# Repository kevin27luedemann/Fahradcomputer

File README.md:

# Fahradcomputer
Programm und andere Sachen fuer den Fahradcomputer

05.09.2015 Bibliotheken und Dataenblaetter hinzu

07.10.2015 MK2 begonnen und Programm portiert

13.12.2015 Softwareversion 3.0 begonnen: mit neuer Oberflächensteuerung

20.01.2016 GPS eingebunden und Aduino Library bereitgestellt

28.01.2016 cluster size von SD kann nicht so klein gewaehlt werden (512), wie muss, nachpruefen und SD gerecht einrichten

30.01.2016 SD Karte funktioniert seid 11:21 Uhr, noch nicht implementitert in FWCP

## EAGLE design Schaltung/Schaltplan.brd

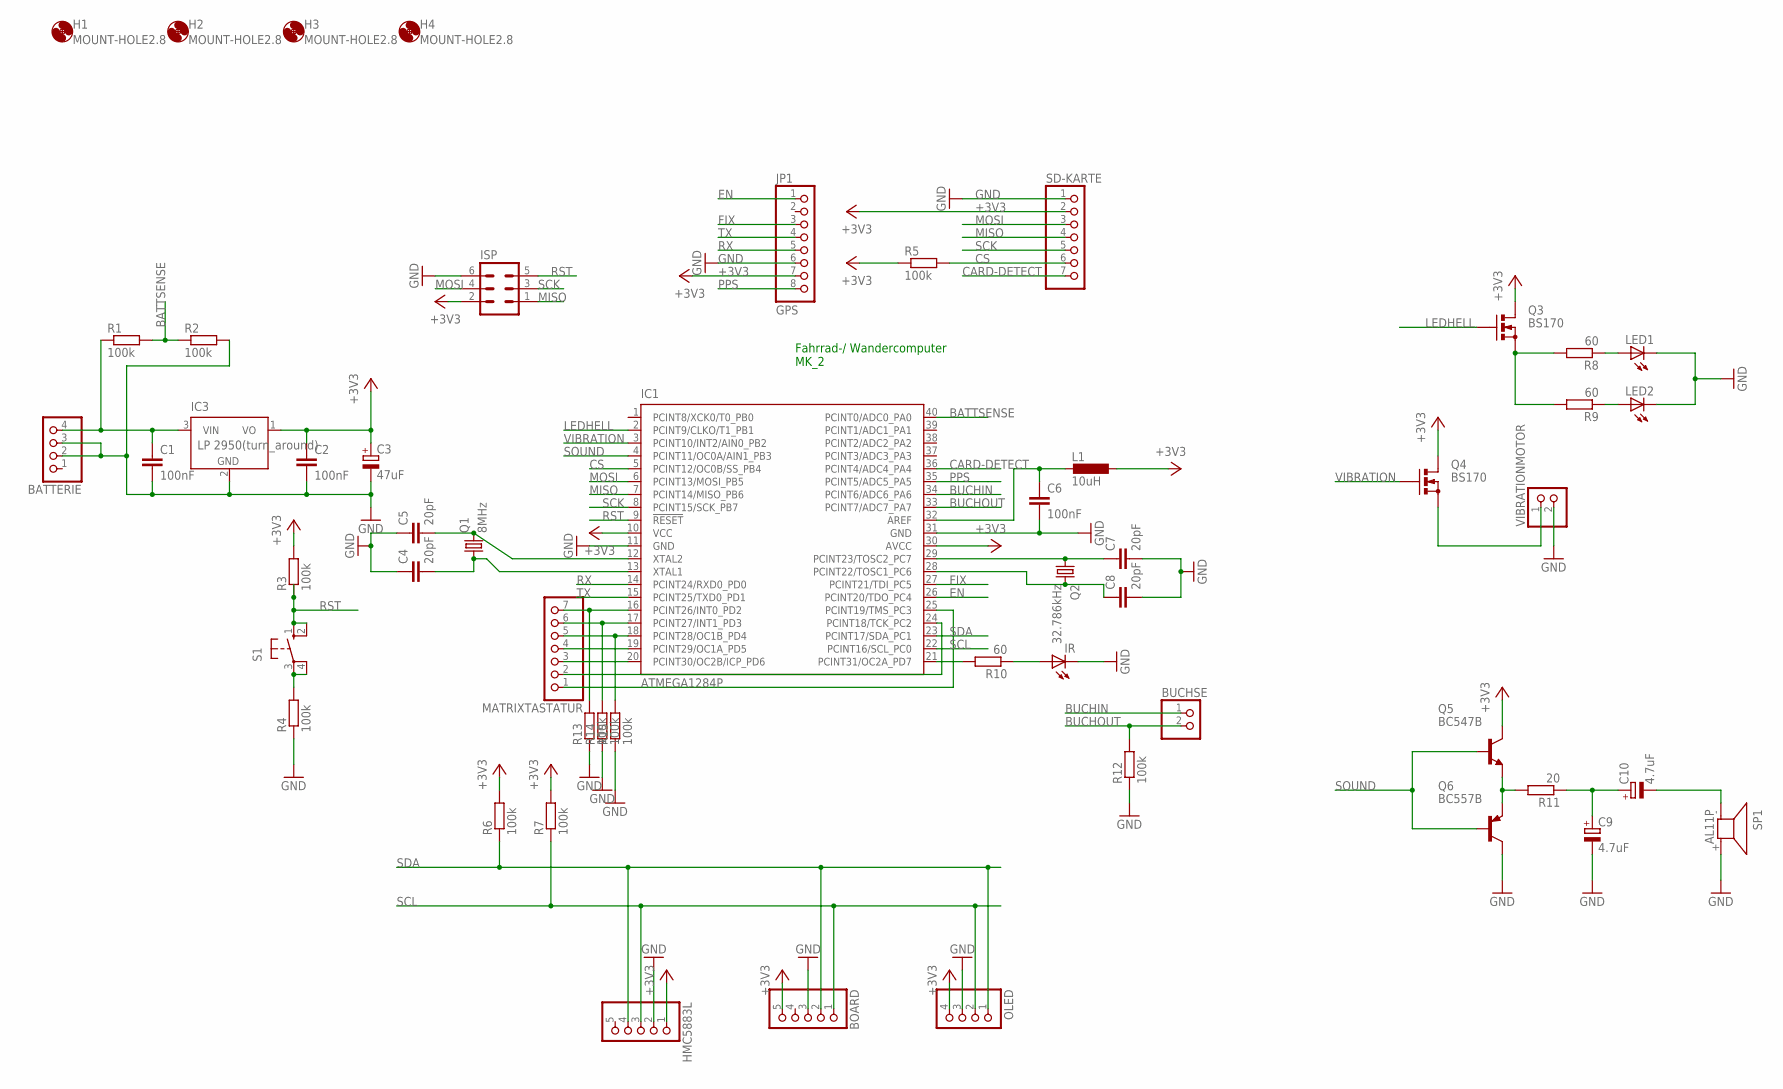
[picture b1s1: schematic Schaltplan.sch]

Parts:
BATTERIE: PINHD-1X4; 1X04
BOARD: PINHD-1X5; 1X05
BUCHSE: PINHD-1X2; 1X02
C1, C2, C6: 100nF; C025-024X044
C3: 47uF; E2,5-6
C4, C5, C7, C8: 20pF; C025-024X044
C9, C10: 4.7uF; E2,5-6
H1, H2, H3, H4: MOUNT-HOLE2.8; 2,8
HMC5883L: PINHD-1X5; 1X05
IC1: ATMEGA1284P; DIL40
IC3: LP 2950(turn_around); TO92
IR: LED3MM
ISP: ML6
JP1: GPS; 1X08
L1: 10uH; 0207/10
LED1, LED2: LED5MM
MATRIXTASTATUR: PINHD-1X7; 1X07
OLED: PINHD-1X4; 1X04
Q1: 8MHz; HC49/S
Q2: 32.786kHz; TC26V
Q3, Q4: BS170; SOT54E
Q5: BC547B; TO92
Q6: BC557B; TO92-EBC
R1, R2, R3, R4, R5, R6, R7, R12, R13, R14, R15: 100k; 0207/10
R8, R9, R10: 60; 0207/10
R11: 20; 0207/10
S1: 10-XX; B3F-10XX
SD-KARTE: PINHD-1X7; 1X07
SP1: AL11P
VIBRATIONMOTOR: PINHD-1X2; 1X02

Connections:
+3V3: BOARD.5, C2.1, C3.+, HMC5883L.1, IC1.10 (VCC), IC1.30 (AVCC), IC3.1 (VO), ISP.2, JP1.7, L1.1, OLED.4, Q3.D, Q4.D, Q5.3 (C), R3.2, R5.1, R6.2, R7.2, SD-KARTE.2
BATTSENSE: IC1.40 (PCINT0/ADC0_PA0), R1.2, R2.1
BUCHIN: BUCHSE.1, IC1.34 (PCINT6/ADC6_PA6)
BUCHOUT: BUCHSE.2, IC1.33 (PCINT7/ADC7_PA7), R12.2
CARD-DETECT: IC1.36 (PCINT4/ADC4_PA4), SD-KARTE.7
CS: IC1.5 (PCINT12/OC0B/SS_PB4), R5.2, SD-KARTE.6
EN: IC1.26 (PCINT20/TDO_PC4), JP1.1
FIX: IC1.27 (PCINT21/TDI_PC5), JP1.3
GND: BATTERIE.2, BATTERIE.3, BOARD.3, C1.2, C2.2, C3.-, C4.1, C5.1, C6.2, C7.2, C8.2, C9.-, HMC5883L.2, IC1.11 (GND), IC1.31 (GND), IC3.2 (GND), IR.K (C), ISP.6, JP1.6, LED1.K (C), LED2.K (C), OLED.3, Q6.C, R2.2, R4.1, R12.1, R13.1, R14.1, R15.1, SD-KARTE.1, SP1.+ (2), VIBRATIONMOTOR.2
LEDHELL: IC1.2 (PCINT9/CLKO/T1_PB1), Q3.G
MISO: IC1.7 (PCINT14/MISO_PB6), ISP.1, SD-KARTE.4
MOSI: IC1.6 (PCINT13/MOSI_PB5), ISP.4, SD-KARTE.3
unnamed: BATTERIE.4, C1.1, IC3.3 (VIN), R1.1
unnamed: C5.2, IC1.12 (XTAL2), Q1.2
unnamed: C7.1, IC1.29 (PCINT23/TOSC2_PC7), Q2.1
unnamed: C4.2, IC1.13 (XTAL1), Q1.1
unnamed: C8.1, IC1.28 (PCINT22/TOSC1_PC6), Q2.2
unnamed: R4.2, S1.3, S1.4 (P1)
unnamed: Q3.S, R8.2, R9.2
unnamed: C6.1, IC1.32 (AREF), L1.2
unnamed: LED1.A, R8.1
unnamed: LED2.A, R9.1
unnamed: IC1.16 (PCINT26/INT0_PD2), MATRIXTASTATUR.7, R13.2
unnamed: IC1.17 (PCINT27/INT1_PD3), MATRIXTASTATUR.6, R14.2
unnamed: IC1.18 (PCINT28/OC1B_PD4), MATRIXTASTATUR.5, R15.2
unnamed: Q4.S, VIBRATIONMOTOR.1
unnamed: IC1.19 (PCINT29/OC1A_PD5), MATRIXTASTATUR.4
unnamed: IC1.20 (PCINT30/OC2B/ICP_PD6), MATRIXTASTATUR.3
unnamed: IC1.24 (PCINT18/TCK_PC2), MATRIXTASTATUR.2
unnamed: IC1.25 (PCINT19/TMS_PC3), MATRIXTASTATUR.1
unnamed: IC1.21 (PCINT31/OC2A_PD7), R10.2
unnamed: IR.A, R10.1
unnamed: Q5.1 (E), Q6.E, R11.2
unnamed: C9.+, C10.+, R11.1
unnamed: C10.-, SP1.- (1)
PPS: IC1.35 (PCINT5/ADC5_PA5), JP1.8
RST: IC1.9 (!RESET), ISP.5, R3.1, S1.1 (S), S1.2 (S1)
RX: IC1.14 (PCINT24/RXD0_PD0), JP1.5
SCK: IC1.8 (PCINT15/SCK_PB7), ISP.3, SD-KARTE.5
SCL: BOARD.1, HMC5883L.3, IC1.22 (PCINT16/SCL_PC0), OLED.2, R7.1
SDA: BOARD.2, HMC5883L.4, IC1.23 (PCINT17/SDA_PC1), OLED.1, R6.1
SOUND: IC1.4 (PCINT11/OC0A/AIN1_PB3), Q5.2 (B), Q6.B
TX: IC1.15 (PCINT25/TXD0_PD1), JP1.4
VIBRATION: IC1.3 (PCINT10/INT2/AIN0_PB2), Q4.G

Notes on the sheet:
Fahrrad-/ Wandercomputer MK_2

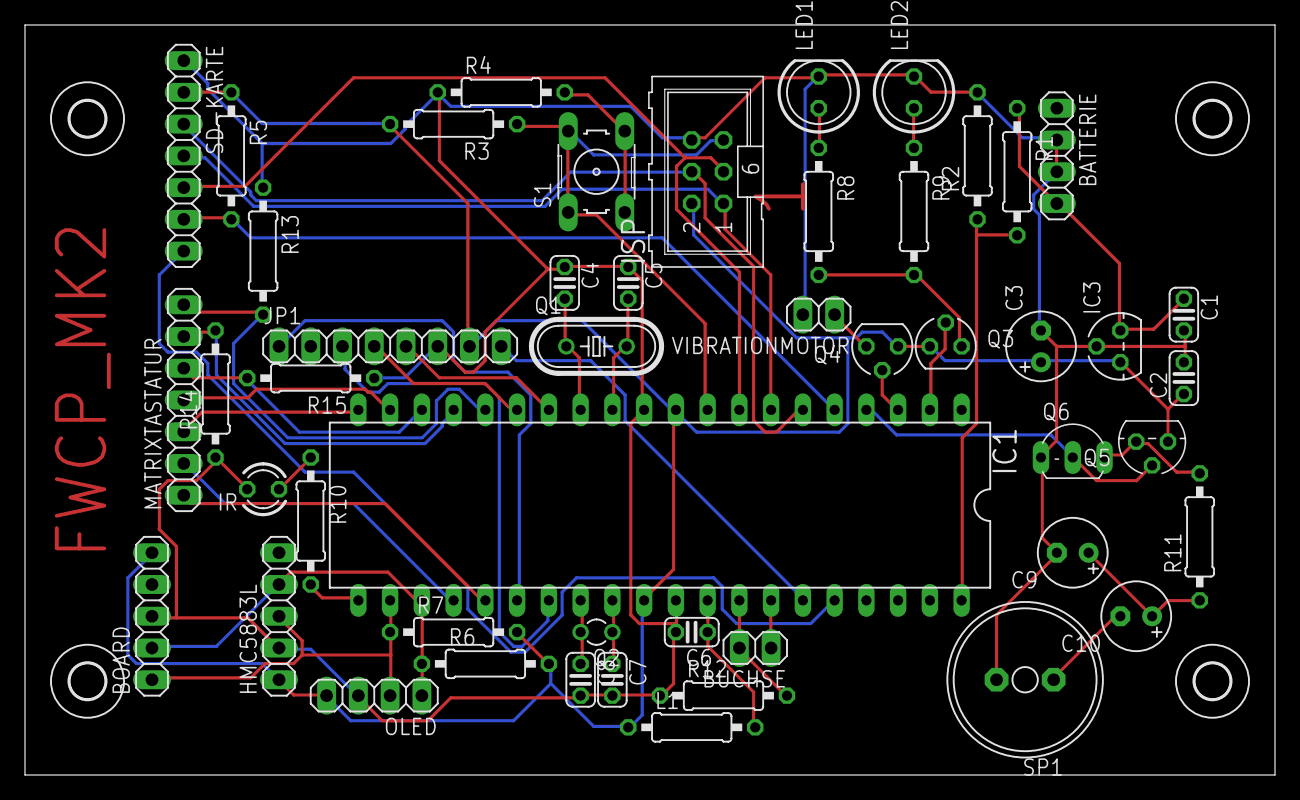
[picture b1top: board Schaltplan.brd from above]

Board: 2 copper layers, 100.0 x 60.0 mm, 53 parts (0 on the bottom side), 44 nets.

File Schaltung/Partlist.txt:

Partlist

Exported from Schaltplan.sch at 18.09.2015 10:32

EAGLE Version 7.3.0 Copyright (c) 1988-2015 CadSoft

Assembly variant: 

Part           Value                Device          Package      Library                 Sheet

BATTERIE                            PINHD-1X4       1X04         pinhead                 1
BOARD                               PINHD-1X5       1X05         pinhead                 1
BUCHSE                              PINHD-1X2       1X02         pinhead                 1
C1             100nF                C-EU025-024X044 C025-024X044 rcl                     1
C2             100nF                C-EU025-024X044 C025-024X044 rcl                     1
C3             47uF                 CPOL-EUE2.5-6   E2,5-6       rcl                     1
C4             20pF                 C-EU025-024X044 C025-024X044 rcl                     1
C5             20pF                 C-EU025-024X044 C025-024X044 rcl                     1
C6             100nF                C-EU025-024X044 C025-024X044 rcl                     1
C7             20pF                 C-EU025-024X044 C025-024X044 rcl                     1
C8             20pF                 C-EU025-024X044 C025-024X044 rcl                     1
C9             4.7uF                CPOL-EUE2.5-6   E2,5-6       rcl                     1
C10            4.7uF                CPOL-EUE2.5-6   E2,5-6       rcl                     1
HMC5883L                            PINHD-1X5       1X05         pinhead                 1
IC1            ATMEGA1284P          ATMEGA644-20PU  DIL40        atmel                   1
IC3            LP 2950(turn_around) LM2936Z-3.0     TO92         national-semiconductor  1
IR                                  LED3MM          LED3MM       led                     1
ISP                                 ML6             ML6          con-ml                  1
JP1            GPS                  PINHD-1X8       1X08         pinhead                 1
L1             10uH                 L-EU0207/10     0207/10      rcl                     1
LED1                                LED5MM          LED5MM       led                     1
LED2                                LED5MM          LED5MM       led                     1
MATRIXTASTATUR                      PINHD-1X7       1X07         pinhead                 1
OLED                                PINHD-1X4       1X04         pinhead                 1
Q1             8MHz                 CRYSTALHC49S    HC49/S       crystal                 1
Q2             32.786kHz            CRYSTALTC26V    TC26V        crystal                 1
Q3             BS170                BS170           SOT54E       transistor-small-signal 1
Q4             BS170                BS170           SOT54E       transistor-small-signal 1
Q5             BC547B               BC547B          TO92         transistor-npn          1
Q6             BC557B               BC557B          TO92-EBC     transistor-pnp          1
R1             100k                 R-EU_0207/10    0207/10      rcl                     1
R2             100k                 R-EU_0207/10    0207/10      rcl                     1
R3             100k                 R-EU_0207/10    0207/10      rcl                     1
R4             100k                 R-EU_0207/10    0207/10      rcl                     1
R5             100k                 R-EU_0207/10    0207/10      rcl                     1
R6             100k                 R-EU_0207/10    0207/10      rcl                     1
R7             100k                 R-EU_0207/10    0207/10      rcl                     1
R8             60                   R-EU_0207/10    0207/10      rcl                     1
R9             60                   R-EU_0207/10    0207/10      rcl                     1
R10            60                   R-EU_0207/10    0207/10      rcl                     1
R11            20                   R-EU_0207/10    0207/10      rcl                     1
R12            100k                 R-EU_0207/10    0207/10      rcl                     1
R13            100k                 R-EU_0207/10    0207/10      rcl                     1
R14            100k                 R-EU_0207/10    0207/10      rcl                     1
R15            100k                 R-EU_0207/10    0207/10      rcl                     1
S1                                  10-XX           B3F-10XX     switch-omron            1
SD-KARTE                            PINHD-1X7       1X07         pinhead                 1
SP1            AL11P                AL11P           AL11P        buzzer                  1
VIBRATIONMOTOR                      PINHD-1X2       1X02         pinhead                 1

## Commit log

2015-09-02 Programmhinzugefuegt
2015-09-05 Programm effizienter
2015-09-05 Fehler behoben
2015-09-06 Programm erweitert
2015-09-06 Datasheet hinzu
2015-09-07 RTC um Kalendermode erweitert und Fehler behoben
2015-09-07 Test
2015-09-07 README erweitert
2015-09-07 Datenblaetter fuer die neuen Sensoren hinzu
2015-09-07 Informationen fuer pedometer hinzugefuegt
2015-09-07 SCL Rate auf 400 kHz
2015-09-08 Class fuer den Drucksensor geschrieben, ohne Mode einstellungen bis jetzt einfuegen, wenn vorhanden und ausprobiert
2015-09-08 Stundenzeiger feinstrucktur ueber Minuten implementiert, zu dem Fehler in Druck behoben
2015-09-09 Fehler in Pressure.h behoben und Class fuer LSM303D angefangen
2015-09-09 datein hinzugefuegt
2015-09-09 Output class erstellt und angewendet auf LED und Vibrationsmotor. Beide in Hardware vorhanden.
2015-09-09 Fehler in Druckberechung nicht behoben
2015-09-10 Druckausganbe funktioniert und Oberflaeche geschrieben
2015-09-17 Altimeter impleentiert
2015-09-17 Materialliste hinzu
2015-09-17 Schaltung hinzugefuegt
2015-09-17 grosse Uhr hinzu
2015-09-17 reichelt Warenkorb hinzu
2015-09-18 Schaltung un d Board verandert
2015-09-18 Schaltplan/Board beim Hersteller hochgeladen
2015-09-18 Schaltplan und Board als PDF
2015-09-22 Licht an/aus eingebaut, strecke und maxgeschw ebenfalls
2015-09-23 neues update und zusaetzliche Fahrtzeit und loeschfunktion fuer die Werte im Speicher
2015-09-27 Oberflaechenverbesserung und Modus erweiterung. Bildsschirm aktualisiert nun so schnell wie moeglich
2015-09-28 Fahrad besser und Funktionsfaehig, noch kein live Test
2015-09-29 Fehler mit updaterate im Fahradmodus behoben. Lngsamfahren erfasst
2015-09-30 Fehler fuer zu hohe Geschwindigkeit behoben
2015-10-01 V.1.42 Wecker eingebaut. Nur einfach, mit einstellbarer Zeit. Nach Ausloesen muss neu aktiviert werden!
2015-10-02 Weckerflagreset Fehler behoben
2015-10-02 Oberflachenupdate fuer die grosse Uhr: Einbau des Batstat
2015-10-02 teile bestellt
2015-10-06 Pokedex begonnen
2015-10-06 pikachu.h
2015-10-06 weiter
2015-10-06 Pikachu hinzu, nur gedreht und gespiegelt
2015-10-06 Skript hinzu
2015-10-08 MK2 begonnen und Programm portiert. Hardware vollstaendig
2015-10-09 Bild von Pikachu erweitert
2015-10-09 Bilder werden jetzt richtig uebersetzt
2015-10-09 neues Bild hinzu
2015-10-09 Glurak hinzu
2015-10-09 weiteres Bild hinzu
2015-10-15 acceleromter funktioniert und tilt compensated compass implementiert
2015-10-15 Rahmen in die Fahradanzeige hinzu
2015-10-15 Code fuer Geschwindigkeit verbessert
2015-10-16 EEPROM Speicherung hinzu und ein paar Fehler behoben beim SOUND(funktionsfaehig)
2015-10-16 Libelle aus ACC daten gebastelt
2015-10-17 SD library hinzu mit beispielen
2015-10-17 Interface parallelisiert mit neen etwa 24 FPS
2015-10-17 Drucksensor faellt aus, da CHIP zertsoert
2015-10-18 Schrittzaehler hinzu, teilweise funktionsbereit
2015-10-26 aktualisiert auf atmelstudio 7
2015-10-29 Game of Life hinzu und begonnen, aber noch zu ineffizient
2015-10-29 Fehler in der Berechung der Summe gefunden
2015-11-25 Schritzaehler loeschbar ueber Taste 0
2015-11-25 Fehler in implementation von eben behoben
2015-11-28 Version 3 begonnen mit ueberarbeitetung des Betriebssystem und interfaces
2015-12-13 Programm erweitert um diplayhandler. Er funktioniert schon zum teil
2015-12-13 Programm erweitert um Tacho und Einstellungen. Es ist jetzt fast wieder vollstaendeig einsatzfaehig
2015-12-13 Arbeit beendet. Einige Seiten fehlen, sowie das Menue und die vollstaendeigen Einstellungen, aber der Handler funktioniert
2015-12-16 mittlere Geschwindigkeit erweitert und Tachoanzeige verbessert
2015-12-16 Readmeupdate
2015-12-16 Menue und Display off hinzu
2015-12-17 Navigationsstrucktur global und funktionsfaehig
2015-12-21 Bilderbearbeitung fuer Pokedex umgeaendert
2015-12-21 Pokedex Bilder wandler erweitert
2016-01-19 GPS sample data hinzu
2016-01-20 GPS implementiert, aber txd und rxd vertauscht, das hab ich ja super hingekriegt
2016-01-21 Arduino Library hinzugefuegt
2016-01-21 Reame erweitert
2016-01-21 Librarys rausgesucht und hinzugefuegt. Sollten jetzt nur nich eingebunden werden
2016-01-21 jetzt auch zeit aus rtc ohne fix
2016-01-21 erster SD versuch teilweise funktioniert, aber nicht im System
2016-01-22 Liberary Fatfs neu hinzu. Arduino geloescht
2016-01-22 GPS funktioniert jetzt sehr gut
2016-01-24 neue Lib hinzu
2016-01-26 speed berechnung in kmh ist drin
2016-01-26 speed error behoben
2016-01-26 GPS fehler behoben
2016-01-26 weiter am sd carte arbeiten
2016-01-27 fehler behoben, aber sd funktioniert immer noch nicht
2016-01-27 Timer ISR in das SD programm hinzugefuegt
2016-01-27 immernoch kein SD support
2016-01-28 sd karte und clustersize muss in programm und sd uebereinstimmen hartpruefen
2016-01-28 SD Karte funktioniert immer noch nicht
2016-01-29 SD tutorial hinzu
2016-01-29 eigenes Abbild
2016-01-29 sd tutorial begonnen
2016-01-29 sd test erweitert
2016-01-29 fix cs low high fault
2016-01-30 eigenes Image hinzu
2016-01-30 dateisystem neu formatiert
2016-01-30 sd ordner hinzu
2016-01-30 sd funktioniert
2016-01-30 sd karte laeuft in simmulation
2016-01-30 Fehler im Projekt behoben
2016-01-30 SD funktionert und logged, wenn nötig die position
2016-01-31 erste test daten hinzu
2016-01-31 aufraeumen
2016-01-31 aufgeraumt
2016-02-01 sd header eingefuegt, um anzeige der stellen
2016-02-01 daten in eine Datei
2016-02-01 gesamte werte verbessert
2016-02-01 Fehler im adden behoben
2016-02-01 temp
2016-02-01 archiev fuer den BIP180 hinzu
2016-02-02 umgeraumt und datenblatt von BMP180 gedurckt
2016-02-02 auswertung hinzu
2016-02-02 drucksensor begonnen
2016-02-03 old commit
2016-02-03 init auf Schlepptron
2016-02-03 main neu aufgeteilt. angefangen Rechenfehler in BMP180 zu beheben
2016-02-04 BMP180 algortithmus ausgebessert
2016-02-04 BMP180 vollstaendig implementiert, aber nicht richtig funktionsfaehig. Ersatz ist bestellt.
2016-02-07 neue Daten
2016-02-08 falschen Zeilenumbruch behoben
2016-02-08 Fehler teilweise behoben, alles in zwei dateien
2016-02-08 strekce als gpx und zusammen
2016-02-08 bearbeitete datein hinzu
2016-02-20 Auschalten des GPS ueber A und B tasten jetzt moeglich
2016-02-27 gps remove wird entfernt
2016-02-28 GPS Movingavvarage hinzu. Fehler in Druckdaten nicht behoben
2016-02-28 Daten des neuen Drucksensors sind jetzt richtig. Berechnungen auch fehlerfrei
2016-02-28 Barometerdaten werden jetzt auch gespeichert
2016-02-28 neue Datenhinzu
2016-02-28 gpx datei erstellt
2016-02-28 Fehler in auswertung behobenc
2016-02-28 Fehler in gps behoben. speichern laeuft noch schief
2016-02-28 speicher problem sollte behoben sein
2016-03-06 Anzeige des GPS in GRAD MINUTEN und SEKUNDEN
2016-03-08 neue Daten der Woche hinzu
2016-03-08 daten in GPX
2016-03-08 fehler in auswertung behoben
2016-03-08 Fehler in letzter Datei behoben
2016-03-08 gpx aus letzter Datei nach fehler behoben 2
2016-03-13 daten hinzu
2016-03-13 gpx erzeugt und hinzu
2016-03-13 Fehler in den Daten behoben
2016-03-25 sprites fuer GPS und Batterie eingefuegt. Version 3.07
2016-03-26 Kompass eingebaut. Nicht tilt Kompesiert
2016-03-27 Batterie moving avv hinzu und GMT +2
2016-04-14 speicherfehler nicht behoben
2017-06-13 programm ok
2017-08-08 added linux make support
2017-08-08 minor changes and alarm clock support
2017-08-08 Add alarm clock
2017-08-08 Add bearing, distance to a set point
2017-08-09 Compass support taks some work
2017-08-10 compass works and bearing also
2017-08-11 Add tillted compass and correct bearing/ heading
2017-08-14 enhanced features
    GPS with Memory
    Rolling Menues
    float save in EEPROM
2017-08-14 Add compile files
2017-08-14 minor bug fix
2017-08-17 some minor bug fixes
2017-08-20 some fuckup
2017-08-20 fuckup undone
2017-08-20 Bug fix
    After Einstellungs Page update Logging was not working.
    LED was some times on after Wecker went out
